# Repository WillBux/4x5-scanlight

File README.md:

# A Better Large Format Light Source For Scanning Color Negative Film

<small>Originally published by [jackw01](https://github.com/jackw01/scanlight) on 2024-08-05, forked 2025-03-20</small>

## tl;dr

Read [Jack's GitHub Page](https://jackw01.github.io/scanlight/) for the theory behind the project.

# Major Changes

This fork is a major redesign of the Scanlight project. 
The main purpose is to expand the size to allow for scanning 4x5 large format film. 

The number of LEDs have been doubled to 12 per color (deep red 660nm; green 525nm; royal blue 450nm) and the 3D printed shroud has been adjusted likewise.
A slightly different [red led](https://www.digikey.ch/en/products/detail/lumileds/L1SP-DRD0002800000/9805570) has been chosen 
to better match the [Spectral-Sensitivity Curve of Portra 160](https://business.kodakmoments.com/sites/default/files/files/resources/e4051_Portra_160.pdf) (and it is cheaper at the time of writing).

This project incorporates a microcontroller (STM32G0B1) which more precisely controls the brightness of each LED channel.
Brightness values can be stored through power off states for repeatable scans. 
Additionally, the microcontroller is responsible for USB-PD (20V is necessary, ~1.25A required for maximum brightness)

[Schematic (PDF)](pcb/schematic.pdf)

[BOM](pcb/bom/ibom.html)

#### Build Notes

The PCB should be fabricated similar to [jackw01/scanlight](https://github.com/jackw01/scanlight), that is a black soldermask and white silkscreen. 

As modified, only a 20V-capable USB PD supply can be used. All parts were sourced on DigiKey.

### The Diffuser

The diffuser stack up has not changed from [jackw01/scanlight](https://github.com/jackw01/scanlight).
Only the 3D printed enclosure has been enlarged. 

I printed the parts in black PETG and installed aluminum tape on the insides to improve efficiency.

Additional parts: 
- 4x M2x6mm socket head cap screws
- 4x M2x10mm socket head cap screws
- 8x M2 square nuts (DIN 562)

### Status and the Future

The backlight has been working great for my scanning! 
I recently redesigned the PCB to add a 2.5mm jack output for a shutter sync.
This enables the ability to scan automatically with separate RGB channels.
This feature is enabled when the 2.5mm jack is plugged in.
I will update the README when my PCBs arrive and I successfully test the feature. 

In the distant future I plan on incorporating this into my enlarger to print 4x5 (and 120) negatives.
I no longer shoot 35mm and probably will not produce a 35mm mask for scanning and printing.
If you only shoot 35mm I recommend using Jack's design as it is smaller and cheaper. 

## license

The PCB schematic, layout, and Gerber files and the 3D CAD files for this project are released under the CERN Open Hardware Licence Version 2 - Weakly Reciprocal (CERN-OHL-W V2).

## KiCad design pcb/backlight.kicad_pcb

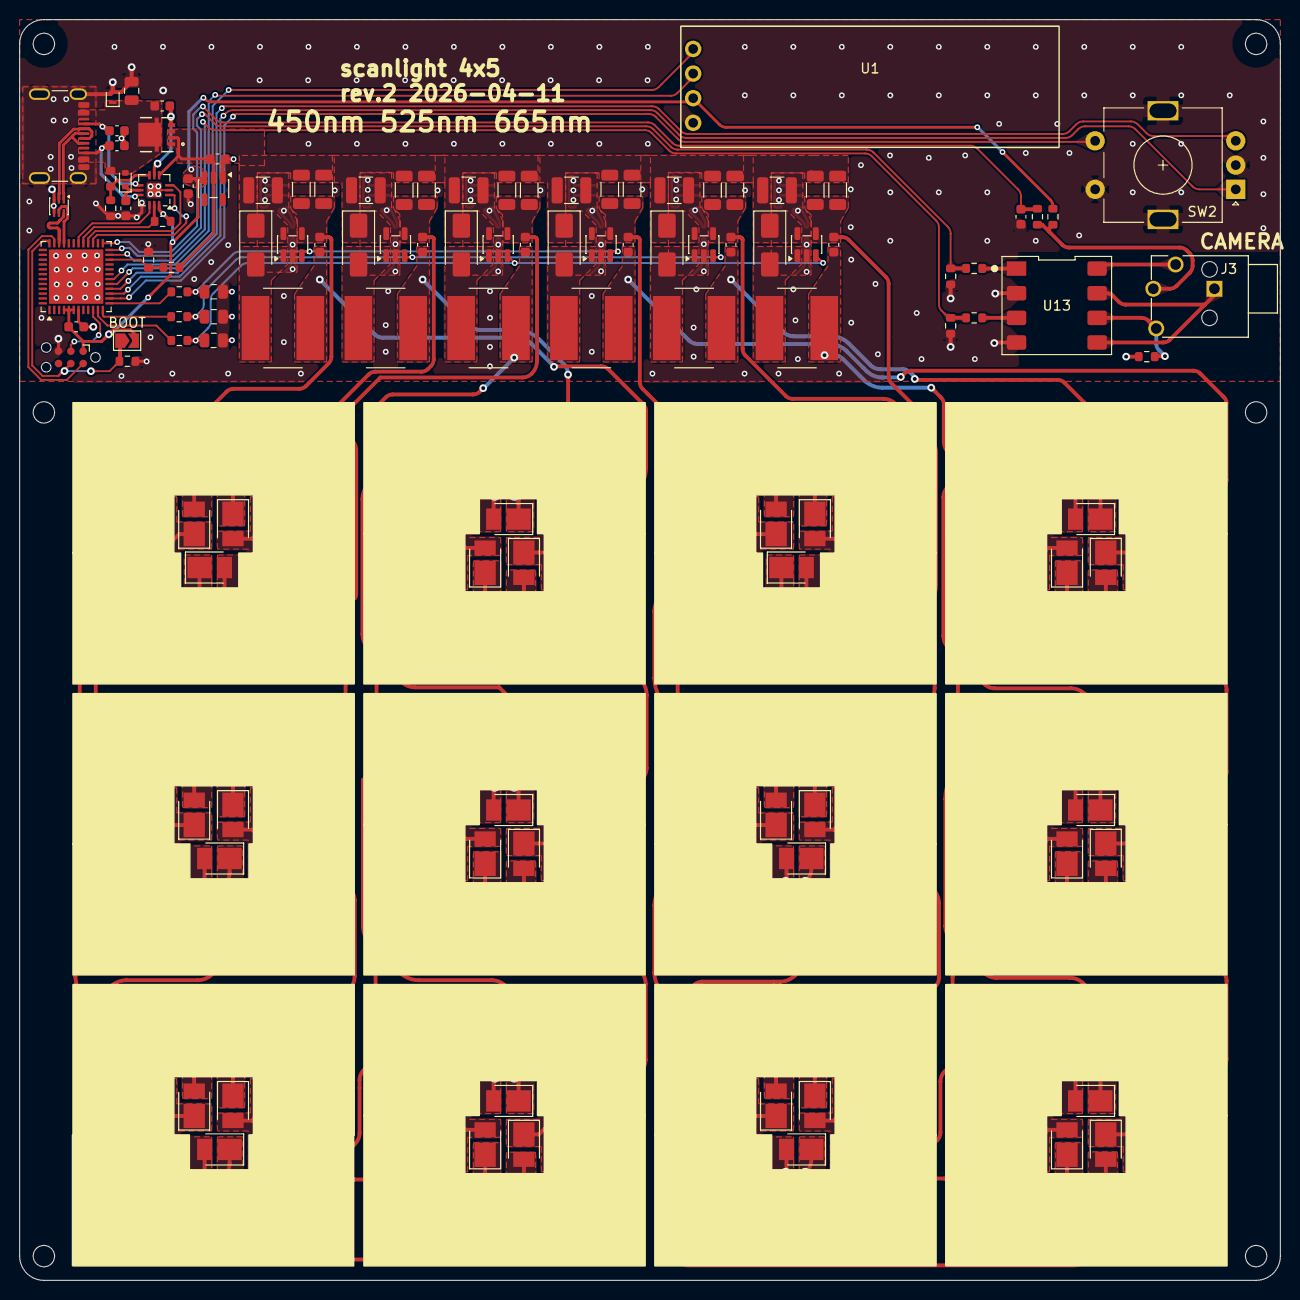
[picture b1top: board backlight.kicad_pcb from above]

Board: 2 copper layers, 130.0 x 130.0 mm, 127 parts (1 on the bottom side), 89 nets.

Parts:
C1, C2: 330p; C_0603_1608Metric
C3: 4.7u; C_0805_2012Metric
C4, C8, C9, C14, C15, C18, C19, C22: 1u; C_0603_1608Metric
C5, C6, C23: 0.1u; C_0603_1608Metric
C7, C11, C13: 47n; C_0805_2012Metric
C10, C12, C16, C17, C20, C21: 10u; C_1210_3225Metric
C24: 680p; C_0603_1608Metric
D1: BAT54K; D_SOD-523
D2: ESDA25P35; ST_QFN-2L_1.6x1.0mm
D3, D4, D6, D7, D8, D21: B240A; D_SMA
D5, D9, D12, D15, D20, D24, D27, D31, D34, D38, D41, D44: red; LED_PLCC_2835_Handsoldering_Reverse
D10, D13, D17, D18, D22, D25, D29, D32, D33, D37, D39, D43: green; LED_PLCC_2835_Handsoldering
D11, D14, D16, D19, D23, D26, D28, D30, D35, D36, D40, D42: blue; LED_PLCC_2835_Handsoldering
H1, H2, H3, H4, H5, H6: MountingHole; MountingHole_2.2mm_M2_Mask_5mm
J1: UJ20-C-H-G-SMT-P16-TR; USB_C_Receptacle_UJ20-C-H-G-SMT-P16-TR
J2: SWD_TC2030; Tag-Connect_TC2030-IDC-NL_2x03_P1.27mm_Vertical
J3: SJ-2504N; CUI_SJ-2504N
L1, L2, L3, L4, L5, L6: 100u; L_Bourns_SRN8040TA
Q1: STL11N3LLH6; POWERFLAT-3p3X3p3_STM
R1, R10, R24, R25: 10k; R_0603_1608Metric
R2: 100k; R_0603_1608Metric
R3: 620; R_0603_1608Metric
R4: 200k; R_0603_1608Metric
R5, R7, R8, R26: 4.7k; R_0603_1608Metric
R6, R11, R12, R13, R14, R15, R16, R17, R18, R19, R20, R21: 845m; R_1206_3216Metric
R9: 40.2k; R_0603_1608Metric
R22, R23: 330; R_0603_1608Metric
R27: 470k; R_0603_1608Metric
R28: 47k; R_0603_1608Metric
SW1: BOOT; SolderJumper-2_P1.3mm_Open_TrianglePad1.0x1.5mm
SW2: RotaryEncoder_Switch_MP; RotaryEncoder_Alps_EC11E-Switch_Vertical_H20mm
SYM1: SYM_Hot_Large; HOT
U1: 0.91 Inch OLED; 0.91_OLED_Display
U2: ECMF02-2AMX6; ST_UQFN-6L_1.5x1.7mm_P0.5mm
U3: STM32G0B1CBUx; QFN-48-1EP_7x7mm_P0.5mm_EP5.6x5.6mm
U4: TCPP01_M12; QFN-12-1EP_3x3mm_P0.50mm_EP1.45x1.45mm
U5, U7, U8, U9, U10, U11: AL8860WT; TSOT-23-5
U6: ST732M33R; TSOT-23-5
U13: AQW212EHAX; DIP-8_W8.3_SMDSocket

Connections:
+3.3V: C6.1, C8.1, J2.1 (VCC), R10.1, R27.2, SW1.2 (B), U1.2 (VCC), U3.4 (VBAT), U3.5 (VREF+), U3.6 (VDD), U4.12 (VCC), U6.3 (Vout)
/ADC_VBUS: R4.2, R9.1, U3.22 (PB10)
/CC1: U3.28 (PA8), U4.3 (CC1)
/CC2: U3.27 (PB15), U4.1 (CC2)
/CTRL_B: C13.1, R8.1, U5.3 (CTRL), U8.3 (CTRL)
/CTRL_G: C11.1, R7.1, U7.3 (CTRL), U10.3 (CTRL)
/CTRL_R: C7.1, R5.1, U9.3 (CTRL), U11.3 (CTRL)
/D+: U2.6 (D+_out), U3.34 (PA10/PA12)
/D-: U2.5 (D-_out), U3.33 (PA9/PA11)
/Focus: R22.2, R25.1, U3.24 (PB12)
/Focus_ISO: J3.4, U13.8
/LED_Blue1/D0: D11.1 (K), D23.2 (A)
/LED_Blue1/D1: D23.1 (K), D35.2 (A)
/LED_Blue1/D2: D35.1 (K), D36.2 (A)
/LED_Blue1/D3: D26.2 (A), D36.1 (K)
/LED_Blue1/D4: D14.2 (A), D26.1 (K)
/LED_Blue1/LC: C9.2, D14.1 (K), L1.1
/LED_Blue1/SW: D3.2 (A), L1.2, U5.1 (SW)
/LED_Blue1/Set: C9.1, D11.2 (A), R6.2, R11.2, U5.4 (SET)
/LED_Blue2/D0: D16.1 (K), D28.2 (A)
/LED_Blue2/D1: D28.1 (K), D40.2 (A)
/LED_Blue2/D2: D40.1 (K), D42.2 (A)
/LED_Blue2/D3: D30.2 (A), D42.1 (K)
/LED_Blue2/D4: D19.2 (A), D30.1 (K)
/LED_Blue2/LC: C14.2, D19.1 (K), L4.1
/LED_Blue2/SW: D6.2 (A), L4.2, U8.1 (SW)
/LED_Blue2/Set: C14.1, D16.2 (A), R12.2, R17.2, U8.4 (SET)
/LED_Green1/D0: D10.1 (K), D22.2 (A)
/LED_Green1/D1: D22.1 (K), D33.2 (A)
/LED_Green1/D2: D33.1 (K), D37.2 (A)
/LED_Green1/D3: D25.2 (A), D37.1 (K)
/LED_Green1/D4: D13.2 (A), D25.1 (K)
/LED_Green1/LC: C15.2, D13.1 (K), L2.1
/LED_Green1/SW: D4.2 (A), L2.2, U7.1 (SW)
/LED_Green1/Set: C15.1, D10.2 (A), R15.2, R16.2, U7.4 (SET)
/LED_Green2/D0: D17.1 (K), D29.2 (A)
/LED_Green2/D1: D29.1 (K), D39.2 (A)
/LED_Green2/D2: D39.1 (K), D43.2 (A)
/LED_Green2/D3: D32.2 (A), D43.1 (K)
/LED_Green2/D4: D18.2 (A), D32.1 (K)
/LED_Green2/LC: C22.2, D18.1 (K), L6.1
/LED_Green2/SW: D8.2 (A), L6.2, U10.1 (SW)
/LED_Green2/Set: C22.1, D17.2 (A), R18.2, R19.2, U10.4 (SET)
/LED_Red1/D0: D5.1 (K), D9.2 (A)
/LED_Red1/D1: D9.1 (K), D12.2 (A)
/LED_Red1/D2: D12.1 (K), D38.2 (A)
/LED_Red1/D3: D34.2 (A), D38.1 (K)
/LED_Red1/D4: D24.2 (A), D34.1 (K)
/LED_Red1/LC: C18.2, D24.1 (K), L3.1
/LED_Red1/SW: D21.2 (A), L3.2, U9.1 (SW)
/LED_Red1/Set: C18.1, D5.2 (A), R13.2, R14.2, U9.4 (SET)
/LED_Red2/D0: D15.1 (K), D27.2 (A)
/LED_Red2/D1: D27.1 (K), D41.2 (A)
/LED_Red2/D2: D41.1 (K), D44.2 (A)
/LED_Red2/D3: D31.2 (A), D44.1 (K)
/LED_Red2/D4: D20.2 (A), D31.1 (K)
/LED_Red2/LC: C19.2, D20.1 (K), L5.1
/LED_Red2/SW: D7.2 (A), L5.2, U11.1 (SW)
/LED_Red2/Set: C19.1, D15.2 (A), R20.2, R21.2, U11.4 (SET)
/NRST: J2.3 (~RESET), U3.10 (PF2)
/PWM_B: R8.2, U3.13 (PA2)
/PWM_G: R7.2, U3.12 (PA1)
/PWM_R: R5.2, U3.11 (PA0)
/Power/CC1c: C2.1, J1.A5 (CC1), U4.7 (CC1c)
/Power/CC2c: C1.1, J1.B5 (CC2), U4.9 (CC2c)
/Power/D0+: J1.A6 (D+), J1.B6 (D+), U2.1 (D+_in)
/Power/D0-: J1.A7 (D-), J1.B7 (D-), U2.2 (D-_in)
/Power/VBUS_CTRL: R1.2, R3.1, U4.6 (VBUS_CTRL)
/R_I: SW2.B, U3.16 (PA5)
/R_Q: SW2.A, U3.15 (PA4)
/R_SW: SW2.S1, U3.14 (PA3)
/SCL: U1.3 (SCL), U3.18 (PA7)
/SDA: U1.4 (SDA), U3.17 (PA6)
/SWCLK: J2.4 (SWCLK), R2.1, SW1.1 (A), U3.36 (PA14)
/SWDIO: J2.2 (SWDIO), U3.35 (PA13)
/Sense: C23.2, R26.2, U3.25 (PB13)
/Shutter: R23.2, R24.1, U3.23 (PB11)
/Shutter_ISO: J3.3, R28.1, U13.6
/TIP_SW: J3.2, R26.1, R27.1
/~DB: U3.30 (PC6), U4.10 (DB/)
/~FLT: R10.2, U3.29 (PA9/UCPD1_DBCC1), U4.11 (FLT/)
GND: C1.2, C2.2, C3.1, C4.1, C5.2, C6.2, C7.2, C8.2, C10.2, C11.2, C12.2, C13.2, C16.2, C17.2, C20.2, C21.2, C23.1, D2.2 (A), J1.A1 (GND), J1.A12 (GND), J1.B1 (GND), J1.B12 (GND), J1.S1 (SHIELD), J2.5 (GND), R2.2, R3.2, R9.2, R24.2, R25.2, R28.2, SW2.C, SW2.MP, SW2.S2, U1.1 (GND), U2.3 (GND), U2.4 (NC), U3.7 (VSS), U3.49 (VSS), U4.2 (GND), U4.13 (GND), U5.2 (GND), U6.1 (GND), U7.2 (GND), U8.2 (GND), U9.2 (GND), U10.2 (GND), U11.2 (GND), U13.2, U13.4
GNDC: J3.1, U13.5, U13.7
unnamed: C5.1, D1.1 (K), U4.8 (IN_GD)
unnamed: R22.1, U13.1
unnamed: R23.1, U13.3
unnamed: C24.2, Q1.4, U4.5 (GATE)
VBUS: C4.2, C10.1, C12.1, C16.1, C17.1, C20.1, C21.1, D3.1 (K), D4.1 (K), D6.1 (K), D7.1 (K), D8.1 (K), D21.1 (K), Q1.1, Q1.2, Q1.3 (S), R4.1, R6.1, R11.1, R12.1, R13.1, R14.1, R15.1, R16.1, R17.1, R18.1, R19.1, R20.1, R21.1, U4.4 (SOURCE), U5.5 (VIN), U6.2 (Vin), U7.5 (VIN), U8.5 (VIN), U9.5 (VIN), U10.5 (VIN), U11.5 (VIN)
VDC: C3.2, C24.1, D1.2 (A), D2.1 (K), J1.A4 (VBUS), J1.A9 (VBUS), J1.B4 (VBUS), J1.B9 (VBUS), Q1.5, Q1.6, Q1.7 (D), Q1.8, R1.1

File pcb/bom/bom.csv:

"Reference","Value","Footprint","Qty","DNP","MPN"
"C1,C2","330p","Capacitor_SMD:C_0603_1608Metric","2","","Generic 330pF 50V C0G/NP0 0603"
"C3","4.7u","Capacitor_SMD:C_0805_2012Metric","1","","Generic 4.7uF 50V X7R 0805 "
"C4,C8,C9,C14,C15,C18,C19,C22","1u","Capacitor_SMD:C_0603_1608Metric","8","","Generic 1uF 50V X7R 0603 X7R"
"C5,C6","0.1u","Capacitor_SMD:C_0603_1608Metric","2","","Generic 0.1uF 50V X7R 0603 "
"C7,C11,C13","47n","Capacitor_SMD:C_0805_2012Metric","3","","Generic 0.047uF 50V X7R 0805"
"C10,C12,C16,C17,C20,C21","10u","Capacitor_SMD:C_1210_3225Metric","6","","Generic 10uF 50V X7R 1210"
"D1","BAT54K","Diode_SMD:D_SOD-523","1","","BAT54KFILM"
"D2","ESDA25P35","Diode_SMD:ST_QFN-2L_1.6x1.0mm","1","","ESDA25P35-1U1M"
"D3,D4,D6,D7,D8,D21","B240A","Diode_SMD:D_SMA","6","","B240A-13-F"
"D5,D9,D12,D15,D20,D24,D27,D31,D34,D38,D41,D44","red","LED_SMD:LED_PLCC_2835_Handsoldering_Reverse","12","","L1SP-DRD0002800000"
"D10,D13,D17,D18,D22,D25,D29,D32,D33,D37,D39,D43","green","LED_SMD:LED_PLCC_2835_Handsoldering","12","","JE2835AGR-N-0002A0000-N0000001"
"D11,D14,D16,D19,D23,D26,D28,D30,D35,D36,D40,D42","blue","LED_SMD:LED_PLCC_2835_Handsoldering","12","","JE2835ARY-N-0002A0000-N0000001"
"J1","UJ20-C-H-G-SMT-P16-TR","Custom:USB_C_Receptacle_UJ20-C-H-G-SMT-P16-TR","1","","UJ20-C-H-G-SMT-P16-TR"
"J2","SWD_TC2030","Connector:Tag-Connect_TC2030-IDC-NL_2x03_P1.27mm_Vertical","1","",""
"L1,L2,L3,L4,L5,L6","100u","Inductor_SMD:L_Bourns_SRN8040TA","6","","HPC 8040NV-101M "
"Q1","STL11N3LLH6","Custom:POWERFLAT-3p3X3p3_STM","1","","STL11N3LLH6"
"R1,R10","10k","Resistor_SMD:R_0603_1608Metric","2","","Generic 10kΩ 5% 0603 "
"R2","100k","Resistor_SMD:R_0603_1608Metric","1","","Generic 100kΩ 1% 0603"
"R3","620","Resistor_SMD:R_0603_1608Metric","1","","Generic 620Ω 1% 0603"
"R4","200k","Resistor_SMD:R_0603_1608Metric","1","","Generic 200kΩ 1% 0603"
"R5,R7,R8","4.7k","Resistor_SMD:R_0603_1608Metric","3","","Generic 4.7kΩ 1% 0603"
"R6,R11,R12,R13,R14,R15,R16,R17,R18,R19,R20,R21","845m","Resistor_SMD:R_1206_3216Metric","12","","Generic 845mΩ 1% 1206"
"R9","40.2k","Resistor_SMD:R_0603_1608Metric","1","","Generic 40.2kΩ 1% 0603"
"SW1","BOOT","Jumper:SolderJumper-2_P1.3mm_Open_TrianglePad1.0x1.5mm","1","",""
"SW2","RotaryEncoder_Switch_MP","Rotary_Encoder:RotaryEncoder_Alps_EC11E-Switch_Vertical_H20mm","1","","EC11E"
"U1","0.91 Inch OLED","Display:0.91_Inch_OLED","1","","Monochrome OLED 0.91"" 128x32 (Aliexpress)"
"U2","ECMF02-2AMX6","Package_DFN_QFN:ST_UQFN-6L_1.5x1.7mm_P0.5mm","1","","ECMF02-2AMX6"
"U3","STM32G0B1CBUx","Package_DFN_QFN:QFN-48-1EP_7x7mm_P0.5mm_EP5.6x5.6mm","1","","STM32G0B1CBU6"
"U4","TCPP01_M12","Custom:QFN-12-1EP_3x3mm_P0.50mm_EP1.45x1.45mm","1","","TCPP01_M12"
"U5,U7,U8,U9,U10,U11","AL8860WT","Package_TO_SOT_SMD:TSOT-23-5","6","","AL8860WT-7"
"U6","ST732M33R","Package_TO_SOT_SMD:TSOT-23-5","1","","ST732M33R"

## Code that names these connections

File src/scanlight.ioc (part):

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Mcu.Name=STM32G0B1C(B-C-E)Ux
Mcu.Package=UFQFPN48
Mcu.UserName=STM32G0B1CBUx
PA0.Signal=S_TIM2_CH1_ETR
PA1.Signal=S_TIM2_CH2
PA11\ [PA9].Mode=Device
PA11\ [PA9].Signal=USB_DM
PA12\ [PA10].Mode=Device
PA12\ [PA10].Signal=USB_DP
PA13.Mode=Serial_Wire
PA13.Signal=SYS_SWDIO
PA14-BOOT0.Mode=Serial_Wire
PA14-BOOT0.Signal=SYS_SWCLK
PA15.Signal=GPIO_Output
PA2.Signal=S_TIM2_CH3
PA3.GPIOParameters=GPIO_PuPd,GPIO_Label
PA3.GPIO_Label=R_SW
PA3.GPIO_PuPd=GPIO_PULLUP
PA3.Signal=GPIO_Input
PA4.GPIOParameters=GPIO_PuPd,GPIO_Label
PA4.GPIO_Label=R_Q
PA4.GPIO_PuPd=GPIO_PULLUP
PA4.Signal=GPIO_Input
PA5.GPIOParameters=GPIO_PuPd,GPIO_Label,GPIO_Mode
PA5.GPIO_Label=R_I
PA5.GPIO_Mode=GPIO_MODE_INPUT
PA5.GPIO_PuPd=GPIO_PULLUP
PA5.Signal=GPIO_Input
PA6.GPIOParameters=GPIO_Pu
PA6.GPIO_Pu=GPIO_PULLUP
PA6.Mode=I2C
PA6.Signal=I2C2_SDA
PA7.GPIOParameters=GPIO_Pu
PA7.GPIO_Pu=GPIO_PULLUP
PA7.Mode=I2C
PA7.Signal=I2C2_SCL
PA8.Mode=Sink_AllSignals
PA8.Signal=UCPD1_CC1
PA9.GPIOParameters=GPIO_Label
PA9.GPIO_Label=FLT_IN
PA9.Signal=GPIO_Input
PB10.GPIOParameters=GPIO_Label
PB10.GPIO_Label=VSENSE
PB10.Mode=IN11
PB10.Signal=ADC1_IN11
PB11.GPIOParameters=GPIO_Label
PB11.GPIO_Label=SHUTTER
PB11.Signal=GPIO_Output
PB12.GPIOParameters=GPIO_Label
PB12.GPIO_Label=FOCUS
PB12.Signal=GPIO_Output
PB13.GPIOParameters=GPIO_Label
PB13.GPIO_Label=CAMERA_DETECT
PB13.Signal=GPIO_Input
PB15.Mode=Sink_AllSignals
PB15.Signal=UCPD1_CC2
PC6.GPIOParameters=PinState,GPIO_Label
PC6.GPIO_Label=DB_OUT
PC6.PinState=GPIO_PIN_RESET
PC6.Signal=GPIO_Output
RCC.HSE_VALUE=8000000
RCC.SYSCLKFreq_VALUE=64000000
RCC.SYSCLKSource=RCC_SYSCLKSOURCE_PLLCLK
board=custom

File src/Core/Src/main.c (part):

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uint8_t bootloaderButtonHeldAtStartup(void) {
	uint32_t start_tick;

	if (HAL_GPIO_ReadPin(R_SW_GPIO_Port, R_SW_Pin) != GPIO_PIN_RESET) {
		return 0U;
	}

	start_tick = HAL_GetTick();
	while ((HAL_GetTick() - start_tick) < BOOTLOADER_BUTTON_HOLD_MS) {
		if (HAL_GPIO_ReadPin(R_SW_GPIO_Port, R_SW_Pin) != GPIO_PIN_RESET) {
			return 0U;
		}
	}
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					>= CAMERA_DETECT_DEBOUNCE_MS)) {
		camera_mode_active = camera_detect_last_sample;
		if (camera_mode_active == 0U) {
			HAL_GPIO_WritePin(SHUTTER_GPIO_Port, SHUTTER_Pin, GPIO_PIN_RESET);
			HAL_GPIO_WritePin(FOCUS_GPIO_Port, FOCUS_Pin, GPIO_PIN_RESET);
		}
	}
}
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}

void EncoderTask(void *argument) {
	uint8_t prev_IQ = ((HAL_GPIO_ReadPin(R_I_GPIO_Port, R_I_Pin) << 1)
			| HAL_GPIO_ReadPin(R_Q_GPIO_Port, R_Q_Pin));
	// for debounce button
	uint8_t lastBtn = HAL_GPIO_ReadPin(R_SW_GPIO_Port, R_SW_Pin);
	uint8_t btnStableState = lastBtn;
	uint32_t btnChangedTime = 0;
	uint8_t currBtn;
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
	for (;;) {
		// rotary FSM
		curr_I = HAL_GPIO_ReadPin(R_I_GPIO_Port, R_I_Pin);
		curr_Q = HAL_GPIO_ReadPin(R_Q_GPIO_Port, R_Q_Pin);
		curr_IQ = (curr_I << 1) | curr_Q;

		index = prev_IQ << 2 | curr_IQ;
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		}

		// Button debounce
		currBtn = HAL_GPIO_ReadPin(R_SW_GPIO_Port, R_SW_Pin);
		if (currBtn != lastBtn) { // button state changed, restart debounce timer
			btnChangedTime = osKernelGetTickCount();
			lastBtn = currBtn;
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  LL_IOP_GRP1_EnableClock(LL_IOP_GRP1_PERIPH_GPIOB);
  LL_IOP_GRP1_EnableClock(LL_IOP_GRP1_PERIPH_GPIOA);
  /**UCPD1 GPIO Configuration
  PB15   ------> UCPD1_CC2
  PA8   ------> UCPD1_CC1
  */
  GPIO_InitStruct.Pin = LL_GPIO_PIN_15;
  GPIO_InitStruct.Mode = LL_GPIO_MODE_ANALOG;
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  __HAL_RCC_GPIOC_CLK_ENABLE();

  /*Configure GPIO pin Output Level */
  HAL_GPIO_WritePin(GPIOB, SHUTTER_Pin|FOCUS_Pin, GPIO_PIN_RESET);

  /*Configure GPIO pin Output Level */
  HAL_GPIO_WritePin(DB_OUT_GPIO_Port, DB_OUT_Pin, GPIO_PIN_RESET);
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  /*Configure GPIO pin Output Level */
  HAL_GPIO_WritePin(GPIOA, GPIO_PIN_15, GPIO_PIN_RESET);

  /*Configure GPIO pins : R_SW_Pin R_Q_Pin R_I_Pin */
  GPIO_InitStruct.Pin = R_SW_Pin|R_Q_Pin|R_I_Pin;
  GPIO_InitStruct.Mode = GPIO_MODE_INPUT;
  GPIO_InitStruct.Pull = GPIO_PULLUP;
  HAL_GPIO_Init(GPIOA, &GPIO_InitStruct);

  /*Configure GPIO pins : SHUTTER_Pin FOCUS_Pin */
  GPIO_InitStruct.Pin = SHUTTER_Pin|FOCUS_Pin;
  GPIO_InitStruct.Mode = GPIO_MODE_OUTPUT_PP;
  GPIO_InitStruct.Pull = GPIO_NOPULL;
  GPIO_InitStruct.Speed = GPIO_SPEED_FREQ_LOW;
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  HAL_GPIO_Init(GPIOA, &GPIO_InitStruct);

  /* USER CODE BEGIN MX_GPIO_Init_2 */
	GPIO_InitStruct.Pin = PWM_R_Pin | PWM_G_Pin | PWM_B_Pin;
	GPIO_InitStruct.Mode = GPIO_MODE_AF_PP;
	GPIO_InitStruct.Pull = GPIO_NOPULL;
	GPIO_InitStruct.Speed = GPIO_SPEED_FREQ_HIGH;
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
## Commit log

2025-03-20 PCB for 4x5 scanlight
2025-03-20 new readme, need to add physical photo
2025-03-20 4x5 version of 3d printed parts
2025-03-20 STM32 Project
2025-06-02 Remove build files
2025-06-02 booting correctly with DFU jump and USBPD working
2025-06-18 Everything finally works, can even save RGB values
    In the future would like to also turn this into a head for an enlarger.
2026-04-17 finalized schematic v2, add GS cap for inrush current
2026-04-17 More stable USBPD code, add camera capture with 2.5mm jack remote
2026-04-28 add custom ssd1306 parameters not in submodule and add .cproject file to ensure the custom defines are included which overwrite the defines in the submodule
2026-04-28 Update readme and current functionality

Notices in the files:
src/Core/Src/main.c:
Copyright (c) 2025 STMicroelectronics.
All rights reserved.
This software is licensed under terms that can be found in the LICENSE file
